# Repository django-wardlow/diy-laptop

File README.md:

# diy-laptop

A diy 15" 2 in 1 based around the framework 13 motherboard

currently in the early stages of development

more details about getting the display working [here](https://community.frame.work/t/connecting-a-wacom-i2c-touchscreen-to-the-framework-13-motherboard-prototype/47499/16)

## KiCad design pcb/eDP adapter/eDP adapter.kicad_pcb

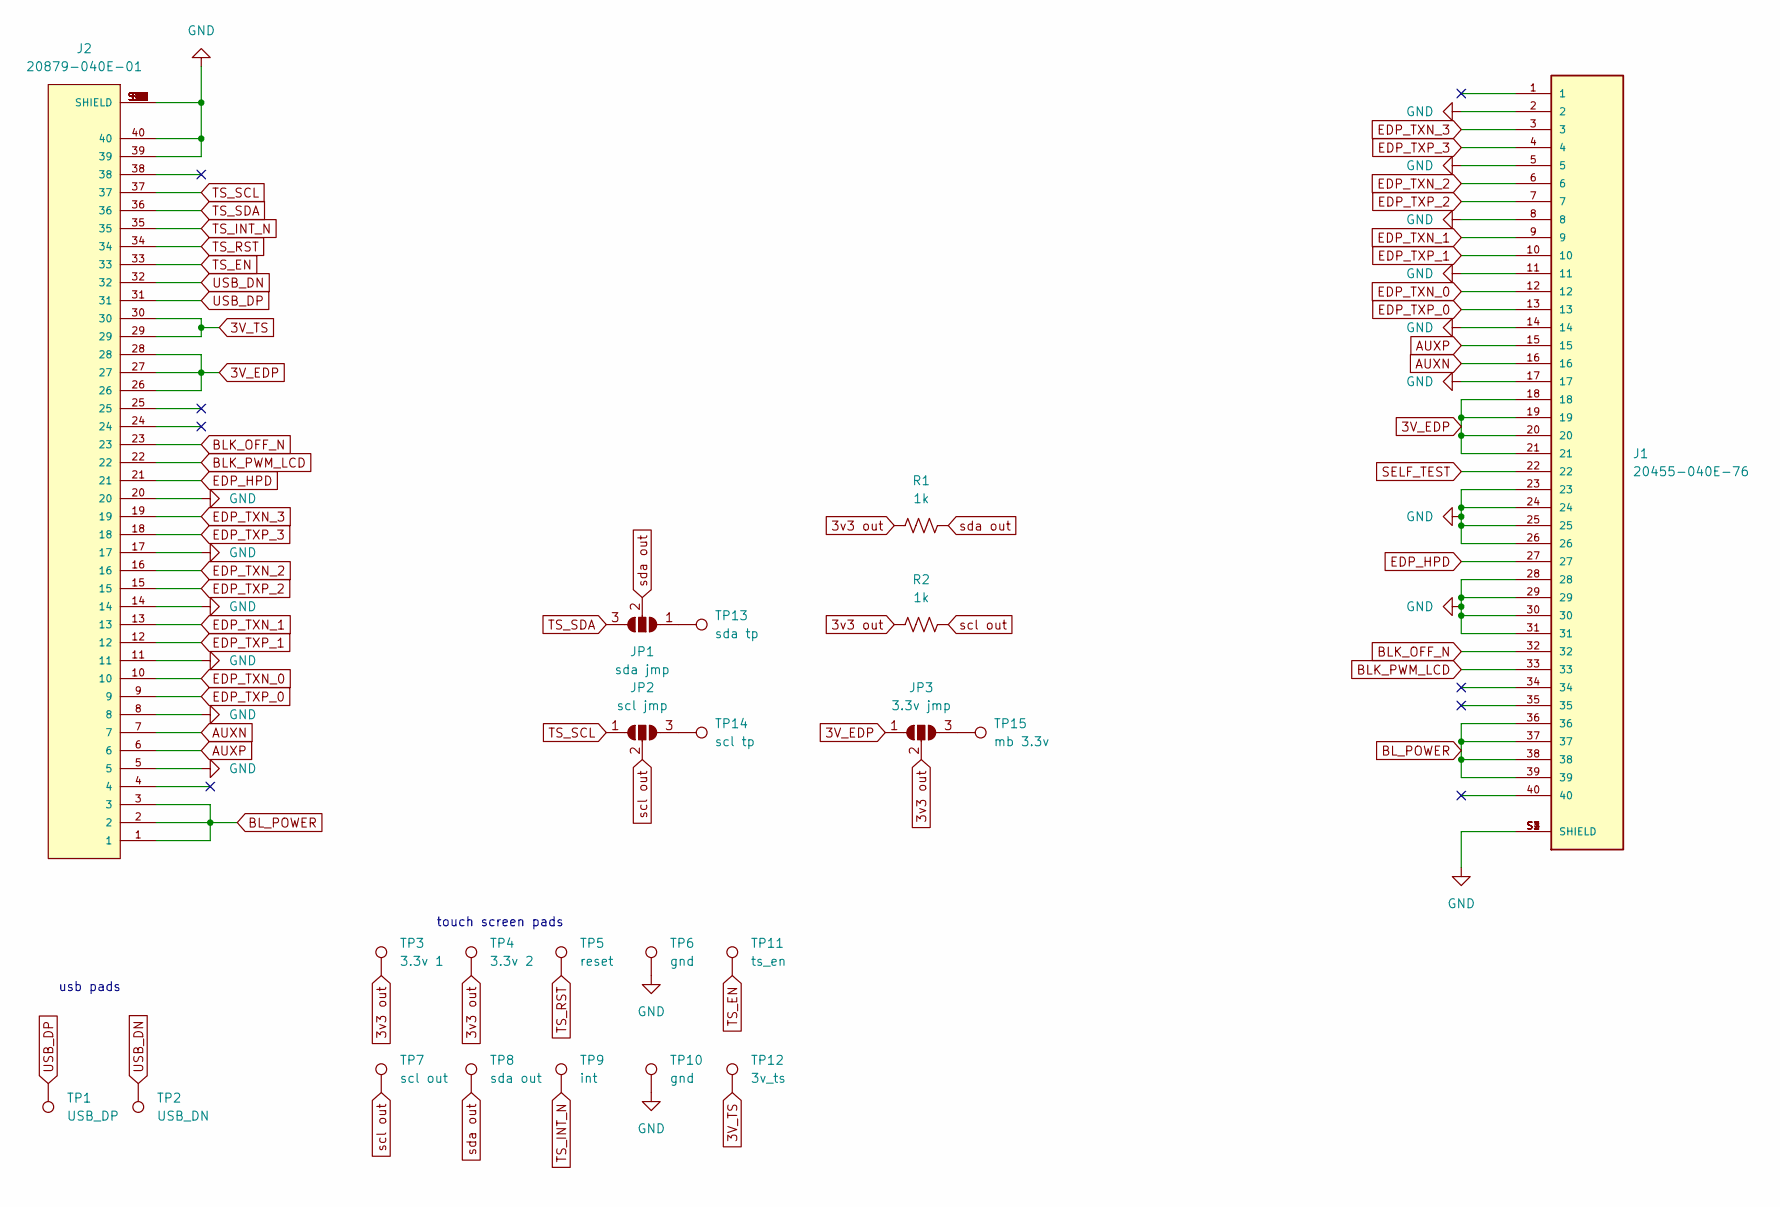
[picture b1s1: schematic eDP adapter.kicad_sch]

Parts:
J1: 20455-040E-76; IPEX_20455-040E-76
J2: 20879-040E-01; IPEX_20879-040E-01; PARTREV 11
JP1: sda jmp; SolderJumper-3_P1.3mm_Open_Pad1.0x1.5mm
JP2: scl jmp; SolderJumper-3_P1.3mm_Open_Pad1.0x1.5mm
JP3: 3.3v jmp; SolderJumper-3_P1.3mm_Open_Pad1.0x1.5mm
R1, R2: 1k; R_1206_3216Metric_Pad1.30x1.75mm_HandSolder
TP1: USB_DP; TestPoint_Pad_D2.0mm
TP2: USB_DN; TestPoint_Pad_D2.0mm
TP3: 3.3v 1; TestPoint_Pad_D2.0mm
TP4: 3.3v 2; TestPoint_Pad_D2.0mm
TP5: reset; TestPoint_Pad_D2.0mm
TP6, TP10: gnd; TestPoint_Pad_D2.0mm
TP7: scl out; TestPoint_Pad_D2.0mm
TP8: sda out; TestPoint_Pad_D2.0mm
TP9: int; TestPoint_Pad_D2.0mm
TP11: ts_en; TestPoint_Pad_D2.0mm
TP12: 3v_ts; TestPoint_Pad_D2.0mm
TP13: sda tp; TestPoint_Pad_D2.0mm
TP14: scl tp; TestPoint_Pad_D2.0mm
TP15: mb 3.3v; TestPoint_Pad_D2.0mm

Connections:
3V_EDP: J1.18, J1.19, J1.20, J1.21, J2.26, J2.27, J2.28, JP3.1 (A)
3V_TS: J2.29, J2.30, TP12.1
3v3 out: JP3.2 (C), R1.2, R2.2, TP3.1, TP4.1
AUXN: J1.16, J2.7
AUXP: J1.15, J2.6
BLK_OFF_N: J1.32, J2.23
BLK_PWM_LCD: J1.33, J2.22
BL_POWER: J1.36, J1.37, J1.38, J1.39, J2.1, J2.2, J2.3
EDP_HPD: J1.27, J2.21
EDP_TXN_0: J1.12, J2.10
EDP_TXN_1: J1.9, J2.13
EDP_TXN_2: J1.6, J2.16
EDP_TXN_3: J1.3, J2.19
EDP_TXP_0: J1.13, J2.9
EDP_TXP_1: J1.10, J2.12
EDP_TXP_2: J1.7, J2.15
EDP_TXP_3: J1.4, J2.18
GND: J1.2, J1.5, J1.8, J1.11, J1.14, J1.17, J1.23, J1.24, J1.25, J1.26, J1.28, J1.29, J1.30, J1.31, J1.S1 (SHIELD), J1.S2 (SHIELD), J1.S3 (SHIELD), J1.S4 (SHIELD), J2.5, J2.8, J2.11, J2.14, J2.17, J2.20, J2.39, J2.40, J2.S1 (SHIELD), J2.S2 (SHIELD), J2.S3 (SHIELD), J2.S4 (SHIELD), J2.S5 (SHIELD), J2.S6 (SHIELD), J2.S7 (SHIELD), J2.S8 (SHIELD), J2.S9 (SHIELD), J2.S10 (SHIELD), J2.S11 (SHIELD), J2.S12 (SHIELD), J2.S13 (SHIELD), J2.S14 (SHIELD), J2.S15 (SHIELD), J2.S16 (SHIELD), J2.S17 (SHIELD), J2.S18 (SHIELD), J2.S19 (SHIELD), J2.S20 (SHIELD), J2.S21 (SHIELD), J2.S22 (SHIELD), J2.S23 (SHIELD), J2.S24 (SHIELD), J2.S25 (SHIELD), J2.S26 (SHIELD), J2.S27 (SHIELD), J2.S28 (SHIELD), J2.S29 (SHIELD), J2.S30 (SHIELD), J2.S31 (SHIELD), J2.S32 (SHIELD), J2.S33 (SHIELD), J2.S34 (SHIELD), TP6.1, TP10.1
unnamed: JP1.1 (A), TP13.1
unnamed: JP2.3 (B), TP14.1
unnamed: JP3.3 (B), TP15.1
SELF_TEST: J1.22
TS_EN: J2.33, TP11.1
TS_INT_N: J2.35, TP9.1
TS_RST: J2.34, TP5.1
TS_SCL: J2.37, JP2.1 (A)
TS_SDA: J2.36, JP1.3 (B)
USB_DN: J2.32, TP2.1
USB_DP: J2.31, TP1.1
scl out: JP2.2 (C), R2.1, TP7.1
sda out: JP1.2 (C), R1.1, TP8.1

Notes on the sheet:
touch screen pads
usb pads

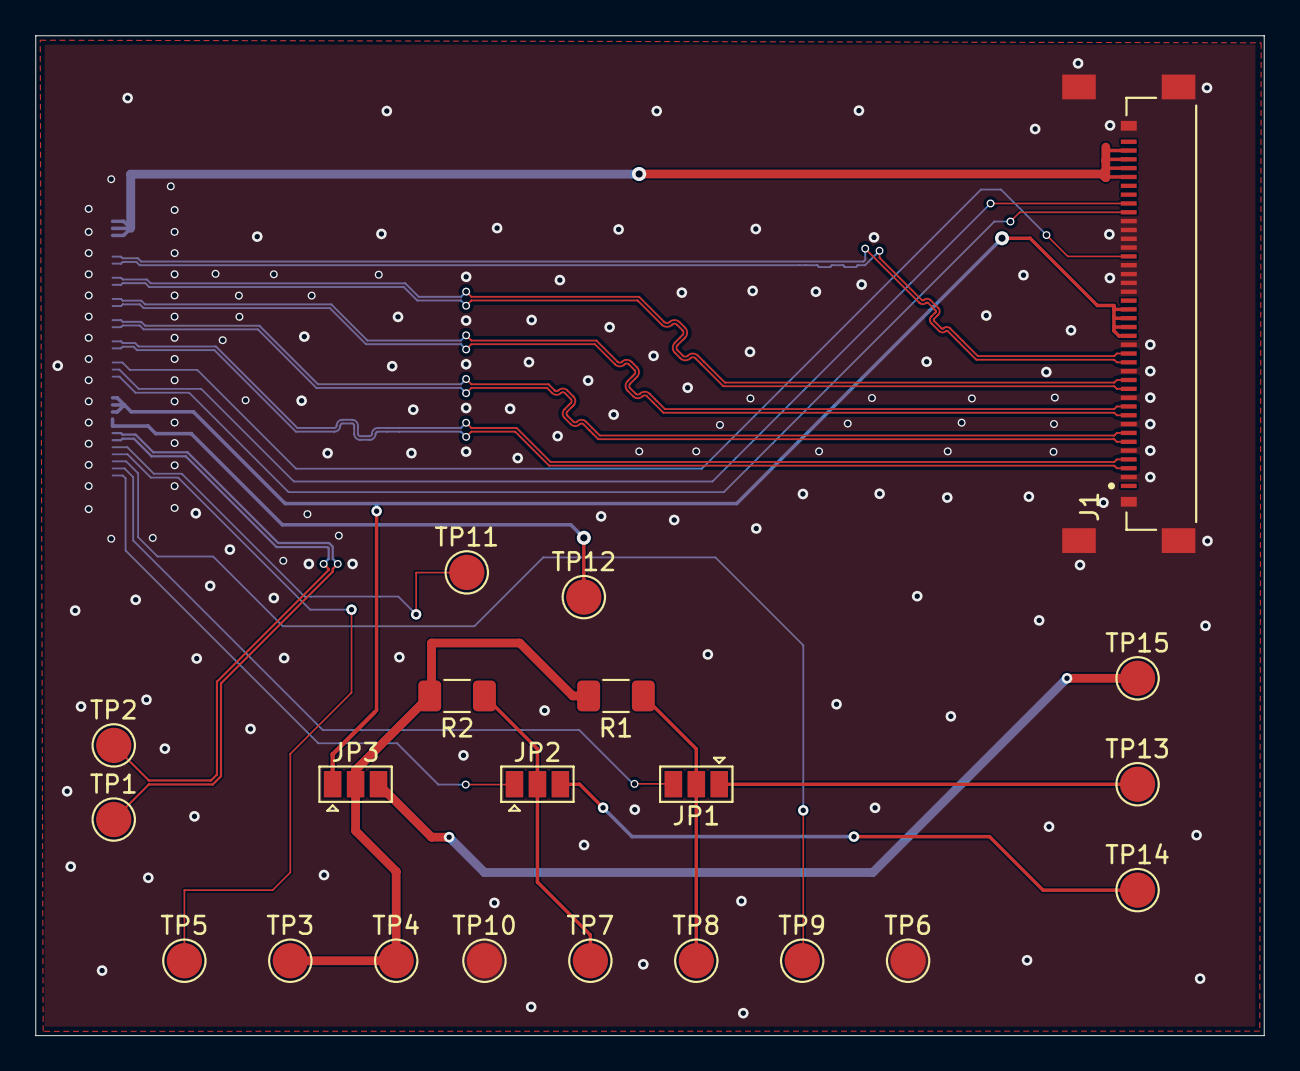
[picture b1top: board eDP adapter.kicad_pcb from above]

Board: 4 copper layers, 69.6 x 56.6 mm, 22 parts (1 on the bottom side), 30 nets.

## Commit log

2024-05-12 added acpi and pcb files
